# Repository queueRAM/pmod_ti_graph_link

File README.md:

# Pmod TI Graph Link breakout board

This repository contains a schematic and PCB layout for a [Pmod](https://digilent.com/reference/pmod/specification)-compatible design that interfaces with TI graphing calculators and peripherals which use the 2.5mm TI graph link connector. The purpose of the board is make it convenient to connect to the calculator DBus without having to solder a cable, provide a convenient pin-out, and to translate the bus voltage to support 3.3V and 5V. The Pmod connectors are very common with FPGA development boards. The board is generic and can be used with any circuit in the 3.3-5V range, such as Arduinos, Raspberry Pis, or homebrew 6502 on breadboards.

The 6-pin Pmod connector supplies VCC, GND, and the two bi-directional tip and ring connections. For each tip and ring there are pull-up resistor, diode, and NPN transistor to allow interfacing with buses of different voltages and out to a 2.5mm stereo TRS jack. The board provisions for an LC low-pass filters for each tip and ring, similar to what is used in the USB silver graph link, TI keyboard, and TI graphing calculators. For debug, the layout provisions for an optional 1x3 header on the DBus side.

## Design

The design optimizes for performance and cost while still being something that
can be hand-soldered. The passives are 0805 or larger, through-hold connectors
were chosen where possible. The diode and transistor are on the smaller pitch,
but were chosen to combine dual components into a single package.

## Bill of Materials (BOM)

REF DES | Footprint | Type            | Manufacturer | Part #           |Qty|
--------|-----------|-----------------|--------------|------------------|---|
J1      | Pmod 0.1" | Pmod Connector  | METZ         | PR20206HBNN      | 1 |
J2      | Custom    | 2.5mm TRS audio | Kycon        | STX-2500-3NTR    | 1 |
J3      | 0.1"      | Debug header*   | METZ         | PR20203VBNN      | 1 |
Q1      | SOT-363   | Bias transistor | Toshiba Semi.| RN1911,LF        | 1 |
D1      | SOT-363   | Schottky diode  | Panjit       | BAT54DW_R1_00001 | 1 |
R1,R2   | 0805      | Pull-up Res.    | YAGEO        | RC0805JR-1310KL  | 2 |
C1,C2   | 0805      | Capacitor*      | YAGEO        | CC0805KRX7R9BB104| 2 |
L1,L2,L3| 1008      | Inductor*       | TDK          | NLV25T-2R7J-EF   | 3 |

(* denotes optional)

 ## Notes

 * [Digilent Pmod specification](https://digilent.com/reference/_media/reference/pmod/pmod-interface-specification-1_3_1.pdf)
 * [TI Graph Link Hardware Protocol](https://www.merthsoft.com/linkguide/hardware.html)
 * [Pmod TI graph link Cemetech forum post](https://www.cemetech.net/forum/viewtopic.php?t=20602)

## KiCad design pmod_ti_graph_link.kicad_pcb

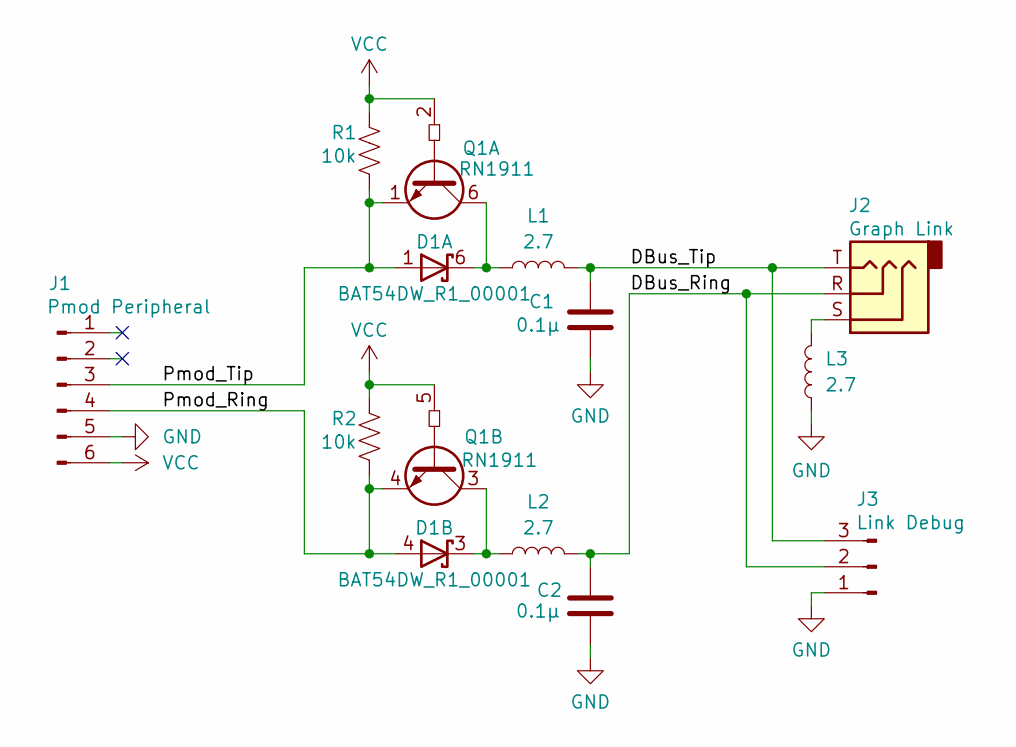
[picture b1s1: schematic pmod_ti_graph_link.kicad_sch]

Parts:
C1, C2: 0.1µ; C_0805_2012Metric_Pad1.18x1.45mm_HandSolder; Digikey 311-1140-1-ND
D1: BAT54DW_R1_00001; SOT-363_SC-70-6; Digikey 3757-BAT54DW_R1_00001CT-ND
J1: Pmod Peripheral; Pmod_1x06_P2.54mm_Horizontal; Digikey 1849-PR20206HBNN-ND
J2: Graph Link; Headphone_Jack_2.5mm_STX-2500-3NTR; Digikey 2092-STX-2500-3NTRCT-ND
J3: Link Debug; PinHeader_1x03_P2.54mm_Vertical; Digikey 1849-1003-ND
L1, L2, L3: 2.7; L_1008_2520Metric_Pad1.43x2.20mm_HandSolder; Digikey 445-16474-1-ND
Q1: RN1911; SOT-363_SC-70-6; Digikey RN1911LF(CTCT-ND
R1, R2: 10k; R_0805_2012Metric_Pad1.20x1.40mm_HandSolder; Digikey 13-RC0805JR-1310KLCT-ND

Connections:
/DBus_Ring: C2.1, J2.R, J3.2, L2.2
/DBus_Tip: C1.1, J2.T, J3.3, L1.2
/Pmod_Ring: D1.4 (A), J1.4, Q1.4 (E2), R2.2
/Pmod_Tip: D1.1 (A), J1.3, Q1.1 (E1), R1.2
GND: C1.2, C2.2, J1.5, J3.1, L3.1
unnamed: D1.6 (K), L1.1, Q1.6 (C1)
unnamed: D1.3 (K), L2.1, Q1.3 (C2)
unnamed: J2.S, L3.2
VCC: J1.6, Q1.2 (B1), Q1.5 (B2), R1.1, R2.1

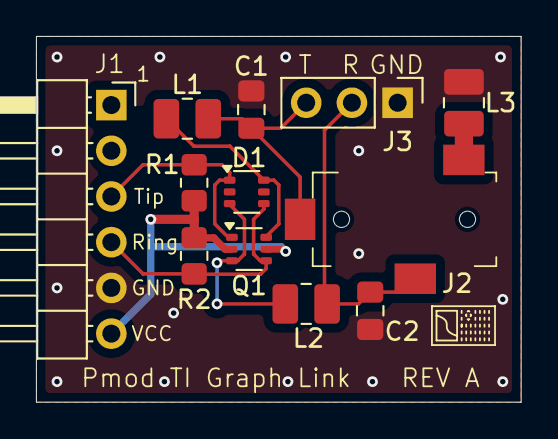
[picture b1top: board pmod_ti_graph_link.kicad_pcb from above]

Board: 2 copper layers, 26.9 x 20.3 mm, 12 parts (0 on the bottom side), 9 nets.

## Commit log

2025-09-10 Initial commit of Pmod board for TI graph link
    - Adds 6-pin Pmod connector to 2.5mm TRS stereo audio
    - Uses biased transistor and diode for level translation
    - Optional LC filter and debug header
2025-09-11 Clean up routing, add GND vias, add text
    - Clean up routing around transistor and diode
    - Add stitching GND vias around perimeter
    - Add "Pmod TI Graph Link" text and date
2025-09-12 Add inductor shield->GND and clean up placement and routing. Prelim "Rev A"
    - Add optional inductor between 2.5mm shield and GND
    - Make VCC thicker, update calc icon, clean up traces
2025-09-16 Add part numbers, README, and images of schematic/PCB/model
    - Add README detailing the project scope and BOM
    - Add image with screenshot of schematic, PCB, and 3D model
    - Specify solder mask and ENIG finish
    - Add Digikey part numbers for reference
